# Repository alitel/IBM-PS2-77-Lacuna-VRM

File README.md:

# IBM-PS2-77-Lacuna-VRM
This is an SMD implementation of a DIY VRM module for the IBM PS/2 Model 77 Lacuna Planar, allowing 100MHz CPU use

This was constructed using the information found here: https://www.ardent-tool.com/76_77/Lacuna_VRM.html

PLEASE NOTE: This is a work in progress and has not been tested yet. I will update this once testing is successful. Use in all cases is at your own risk.

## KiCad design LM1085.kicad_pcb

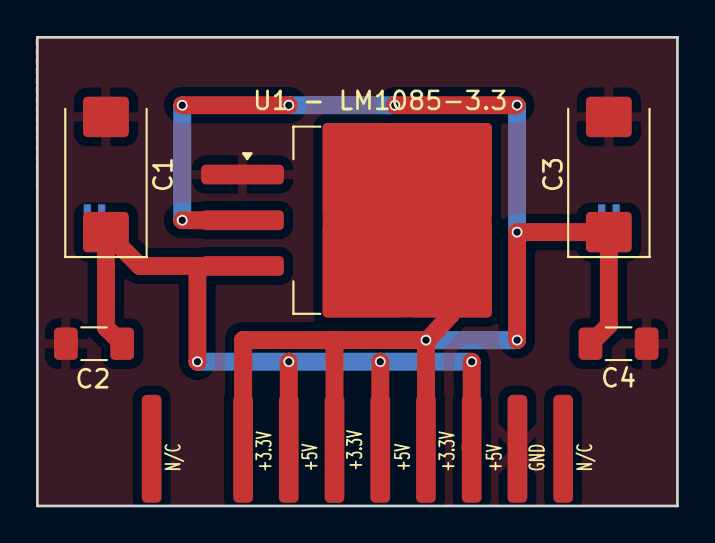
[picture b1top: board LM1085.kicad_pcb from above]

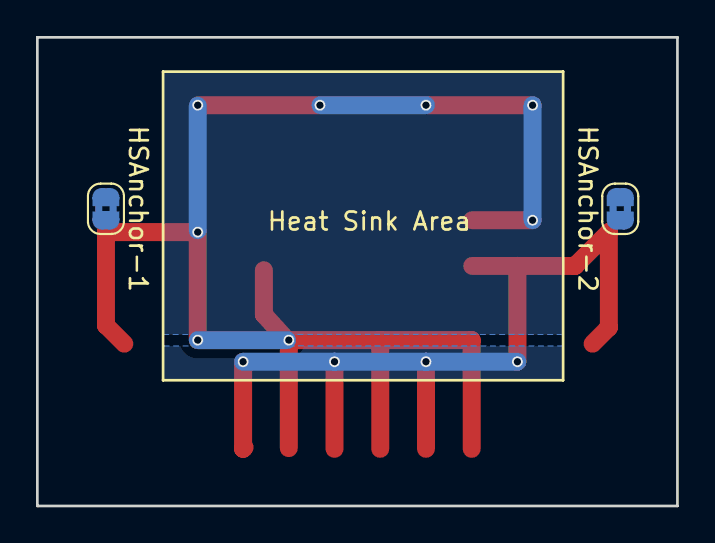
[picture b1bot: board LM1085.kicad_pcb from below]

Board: 2 copper layers, 35.6 x 26.0 mm, 8 parts (2 on the bottom side), 3 nets.

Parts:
C1, C3: CP1; CP_EIA-7343-31_Kemet-D_Pad2.25x2.55mm_HandSolder
C2, C4: C; C_1206_3216Metric_Pad1.33x1.80mm_HandSolder
HSAnchor-1, HSAnchor-2: SolderJumper-2_P1.3mm_Bridged2Bar_RoundedPad1.0x1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; SolderJumper-2_P1.3mm_Bridged2Bar_RoundedPad1.0x1.5mm
U1 - LM1085-3.3: LM1085-3.3; TO-263-3_TabPin2
VRMEdgeConn: VRM_Edge_Conn

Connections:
+3.3V: C3.1, C4.1, U1 - LM1085-3.3.2 (VO), VRMEdgeConn.VC2, VRMEdgeConn.VC4, VRMEdgeConn.VC6
+5V: C1.1, C2.1, U1 - LM1085-3.3.3 (VI), VRMEdgeConn.VC3, VRMEdgeConn.VC5, VRMEdgeConn.VC7
GND: C1.2, C2.2, C3.2, C4.2, U1 - LM1085-3.3.1 (GND), VRMEdgeConn.VC8
